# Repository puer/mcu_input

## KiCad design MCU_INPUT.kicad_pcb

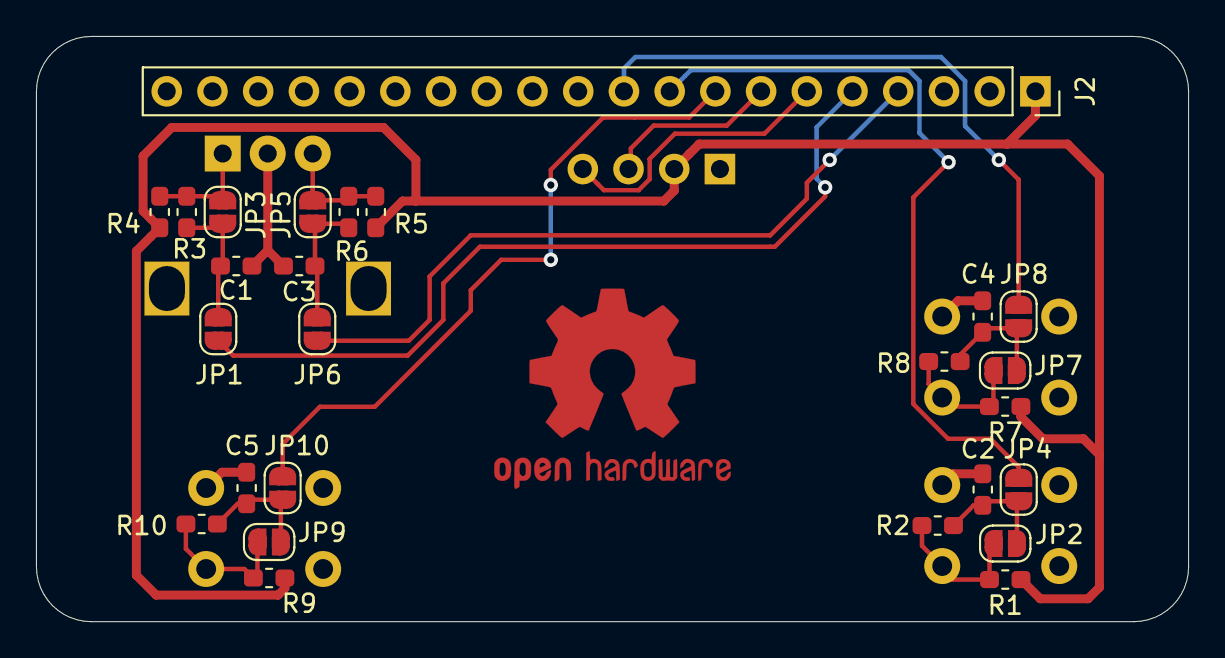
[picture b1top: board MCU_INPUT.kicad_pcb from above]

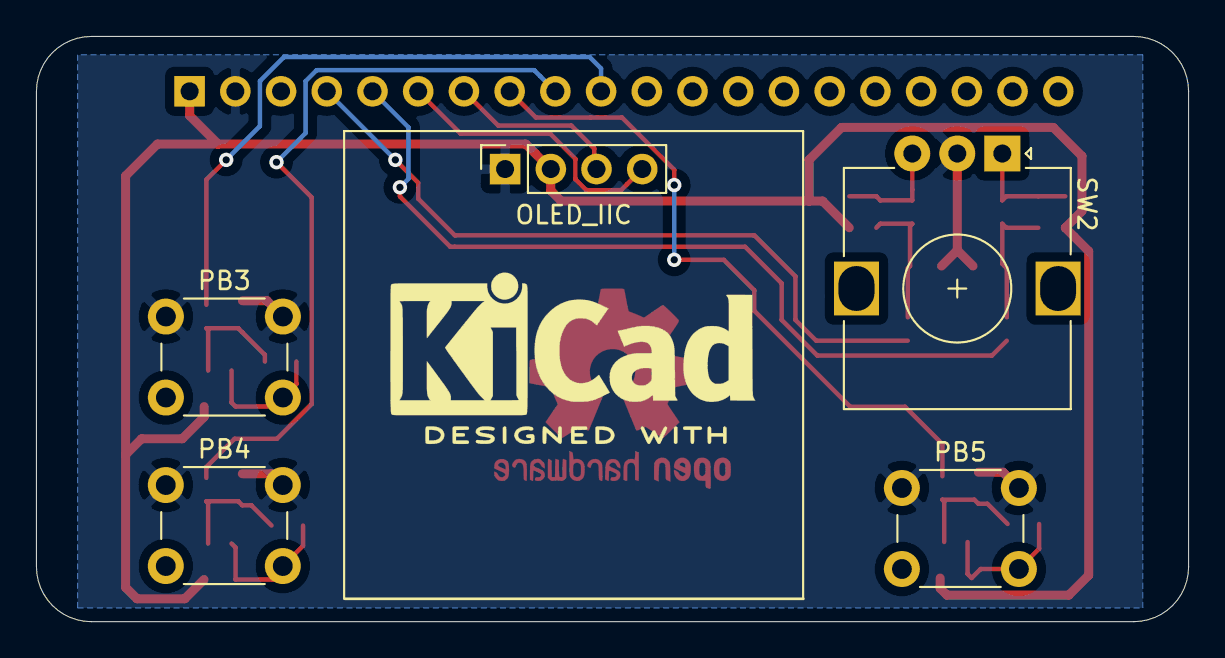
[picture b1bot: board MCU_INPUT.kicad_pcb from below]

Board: 2 copper layers, 64.0 x 32.5 mm, 31 parts (5 on the bottom side), 19 nets.

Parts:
C1, C2, C3, C4, C5: 104; C_0603_1608Metric_Pad1.05x0.95mm_HandSolder
J2: Conn_01x20_Female; PinSocket_1x20_P2.54mm_Vertical
JP1, JP2, JP3, JP4, JP5, JP6, JP7, JP8, JP9, JP10: SolderJumper_2_Open; SolderJumper-2_P1.3mm_Open_RoundedPad1.0x1.5mm
OLED_IIC: Conn_01x04_Female; PinSocket_1x04_P2.54mm_Vertical
PB3, PB4, PB5: SW_Push; SW_PUSH_6mm_H5mm
R1, R2, R3, R4, R5, R6, R7, R8, R9, R10: 10K; R_0603_1608Metric_Pad1.05x0.95mm_HandSolder
SW2: Rotary_Encoder; RotaryEncoder_Alps_EC12E_Vertical_H20mm

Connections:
/PB3: J2.10, JP8.2
/PB4: J2.9, JP4.2
/PB5: J2.8, JP10.2
/PB6: J2.7, OLED_IIC.3
/PB7: J2.6, OLED_IIC.4
/PB8: J2.5, JP1.1
/PB9: J2.4, JP6.2
GND: C1.2, C2.2, C3.2, C4.2, C5.2, J2.2, OLED_IIC.1, PB3.1, PB4.1, PB5.1, SW2.C
unnamed: C1.1, JP1.2, JP3.1, R3.2
unnamed: C2.1, JP2.2, JP4.1, R2.1
unnamed: C3.1, JP5.2, JP6.1, R6.1
unnamed: C4.1, JP7.2, JP8.1, R8.1
unnamed: C5.1, JP9.2, JP10.1, R10.1
unnamed: JP2.1, PB4.2, R1.2, R2.2
unnamed: JP3.2, R3.1, R4.2, SW2.A
unnamed: JP5.1, R5.2, R6.2, SW2.B
unnamed: JP7.1, PB3.2, R7.2, R8.2
unnamed: JP9.1, PB5.2, R9.2, R10.2
VCC: J2.1, OLED_IIC.2, R1.1, R4.1, R5.1, R7.1, R9.1

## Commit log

2019-10-14 init
2019-10-14 ordered
